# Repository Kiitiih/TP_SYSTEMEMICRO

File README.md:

CAMARA - DEMAN
3DN - TP1
---------------------------------------------------------------------------------------------------

rate baud 115200 db

13. PB9 est relié à la masse pour faire le boot_flash et donc il faut une resistance de pull-down

14. Il permet de faire le filtrage du 3.3v pour créer le 3.3VA

*******1.3. sCHÉMA
3. Page 3 / tableau operating conditions (0.47uF typ)

5. Page 15 (100n/10u)

6. CS : Chip Select (0 pour activer l'horloge)
   nLDAC : Latch Dac Input (sert à déclencher la transmission)

7. MISO n'est pas utilisé car il existe pas sur le DAC MCP4801

10. Page 19 datasheet STLINK V3 MINI

*******1.4. Affectation des empreintes

3. 0805, 0603, 1206 : c'est la taille des boitiers

4. LQFT (Low Pofile Quad Pad) : pin sur les 4 cotes du package avec un espacemenet variable mais une hauteur de 1.4mm

SOIC (Small Outline Integrated Circuit) : pin spacing 1.27mm qui sortent des deux cotés du composant

SOT-223 (Small Outline Transistor) : souvent utlisé pour les transistors et les diodes et souvent
3 pins

--------------------------------------------------------------------------------------------------------
3.1. Activation des LL drivers

2. Les différences observées c'est qu'on est plus proche du matériel donc il fut connaitre son microC donc l'intérêt c'est donne des accès direct au reagistre et donc il consomme moins en mémoire Flash et en mémoire dynamique

3.2 LED simple
2. Le prescaler vaut 255.
On a une freq de 32MHz sur les Timer et on veut une résolution sur 8 bits (on compte donc jusqu'à 255)
On fait 32MHz / 255 = 125,5MHz 
Donc prescaler = 125,5MHz / freq (1MHz)= 125
Avec counter period pour le PWM = 255

3.3 LED avec timer

La routine d'interruption se situe dans le fichier stm32L0xx_it.c. Ce qu'il manque par rapport au code genéré par la HAL, c'est la mise à 0 du flag d'interruption. C'est dramatique car si il ne repasse pas à 0, on ne sort jamais de l'interruption. Pour mettre le flag à 0, on utilise la fonction LL_TIM_ClearFlag_UPDATE(TIM21);

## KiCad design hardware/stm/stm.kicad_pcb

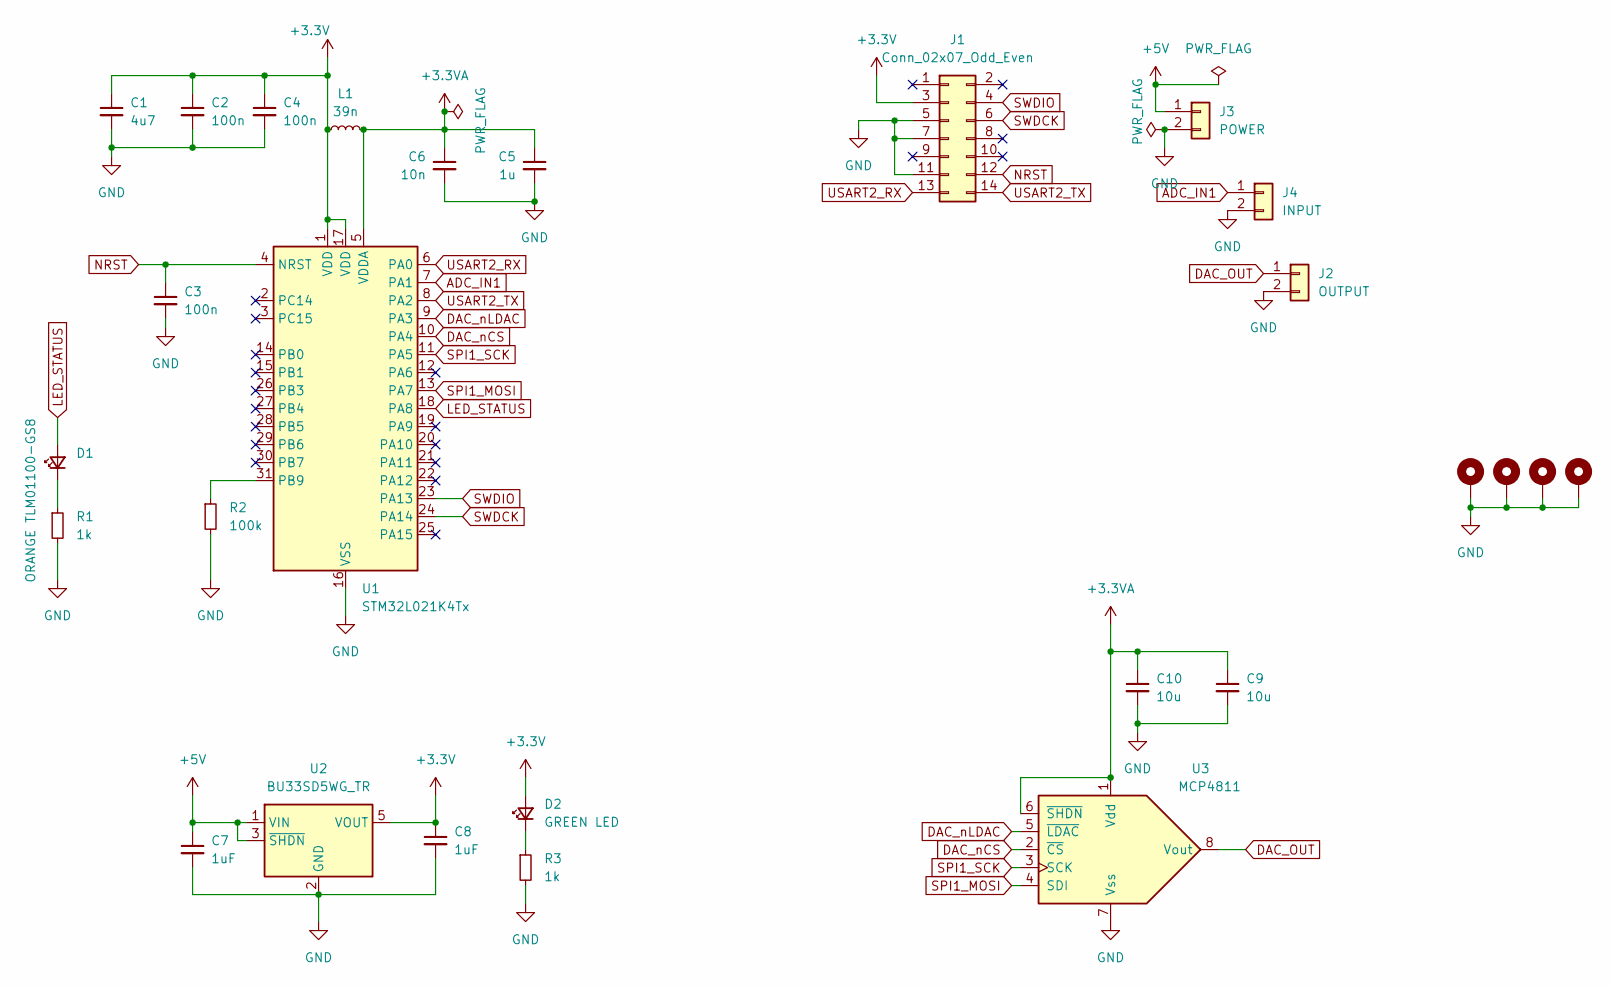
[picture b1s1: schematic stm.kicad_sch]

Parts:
C1: 4u7; LED_0603_1608Metric_Pad1.05x0.95mm_HandSolder
C2, C3, C4: 100n; C_0805_2012Metric_Pad1.18x1.45mm_HandSolder
C5: 1u; C_0805_2012Metric_Pad1.18x1.45mm_HandSolder
C6: 10n; C_0805_2012Metric
C7, C8: 1uF; C_0805_2012Metric
C9, C10: 10u; C_0805_2012Metric_Pad1.18x1.45mm_HandSolder
D1: ORANGE TLM01100-GS8; LED_0603_1608Metric_Pad1.05x0.95mm_HandSolder
D2: GREEN LED; LED_0603_1608Metric_Pad1.05x0.95mm_HandSolder
H101, H102, H103, H104: MountingHole_Pad; MountingHole_3.2mm_M3_Pad
J1: Conn_02x07_Odd_Even; PinHeader_2x07_P1.27mm_Vertical_SMD
J2: OUTPUT; JST_XH_B2B-XH-A_1x02_P2.50mm_Vertical
J3: POWER; JST_XH_B2B-XH-A_1x02_P2.50mm_Vertical
J4: INPUT; JST_XH_B2B-XH-A_1x02_P2.50mm_Vertical
L1: 39n; L_0805_2012Metric_Pad1.05x1.20mm_HandSolder
R1, R3: 1k; R_0805_2012Metric_Pad1.20x1.40mm_HandSolder
R2: 100k; R_0805_2012Metric_Pad1.20x1.40mm_HandSolder
U1: STM32L021K4Tx; LQFP-32_7x7mm_P0.8mm
U2: BU33SD5WG_TR; SOT-23-5
U3: MCP4811; SOIC-8_3.9x4.9mm_P1.27mm

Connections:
+3.3V: C1.1, C2.1, C4.1, C8.1, D2.2 (A), J1.3, L1.2, U1.1 (VDD), U1.17 (VDD), U2.5 (VOUT)
+3.3VA: C5.1, C6.1, C9.1, C10.1, L1.1, U1.5 (VDDA), U3.1 (Vdd), U3.6 (~SHDN)
+5V: C7.1, J3.1, U2.1 (VIN), U2.3 (~SHDN)
ADC_IN1: J4.1, U1.7 (PA1)
DAC_OUT: J2.1, U3.8 (Vout)
DAC_nCS: U1.10 (PA4), U3.2 (~CS)
DAC_nLDAC: U1.9 (PA3), U3.5 (~LDAC)
GND: C1.2, C2.2, C3.2, C4.2, C5.2, C6.2, C7.2, C8.2, C9.2, C10.2, H101.1, H102.1, H103.1, H104.1, J1.5, J1.7, J1.11, J2.2, J3.2, J4.2, R1.2, R2.2, R3.2, U1.16 (VSS), U1.32 (VSS), U2.2 (GND), U3.7 (Vss)
LED_STATUS: D1.2 (A), U1.18 (PA8)
NRST: C3.1, J1.12, U1.4 (NRST)
unnamed: D1.1 (K), R1.1
unnamed: D2.1 (K), R3.1
unnamed: R2.1, U1.31 (PB9)
SPI1_MOSI: U1.13 (PA7), U3.4 (SDI)
SPI1_SCK: U1.11 (PA5), U3.3 (SCK)
SWDCK: J1.6, U1.24 (PA14)
SWDIO: J1.4, U1.23 (PA13)
USART2_RX: J1.13, U1.6 (PA0)
USART2_TX: J1.14, U1.8 (PA2)

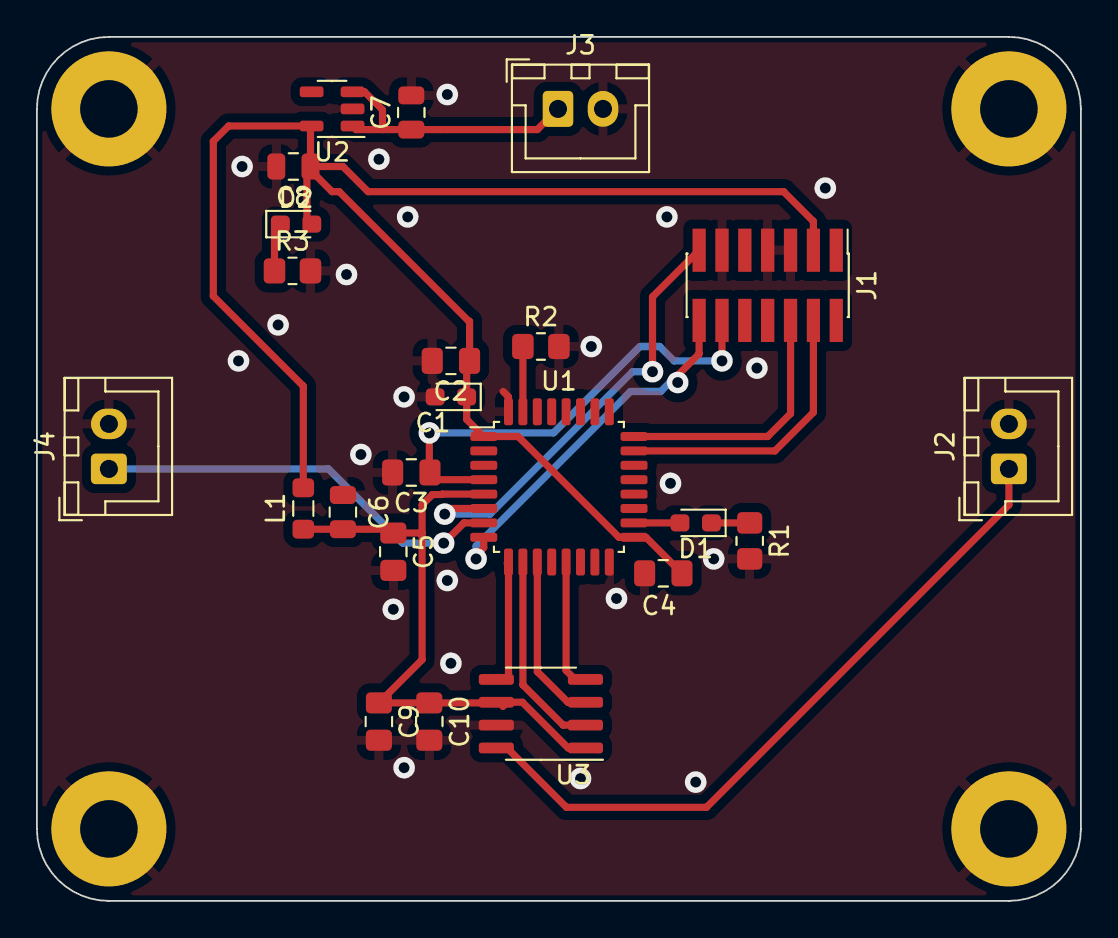
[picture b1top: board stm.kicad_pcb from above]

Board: 2 copper layers, 58.0 x 48.0 mm, 27 parts (0 on the bottom side), 19 nets.

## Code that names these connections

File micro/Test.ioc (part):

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Mcu.Name=STM32L021K4Tx
Mcu.Package=LQFP32
Mcu.UserName=STM32L021K4Tx
PA0-CK_IN.Mode=Asynchronous
PA0-CK_IN.Signal=USART2_RX
PA1.Mode=IN1
PA1.Signal=ADC_IN1
PA13.Mode=Serial_Wire
PA13.Signal=SYS_SWDIO
PA14.Mode=Serial_Wire
PA14.Signal=SYS_SWCLK
PA2.Mode=Asynchronous
PA2.Signal=USART2_TX
PA3.GPIOParameters=GPIO_Label
PA3.GPIO_Label=DAC_nLDAC
PA3.Signal=GPIO_Output
PA4.GPIOParameters=GPIO_Label
PA4.GPIO_Label=DAC_nCS
PA4.Signal=GPIO_Output
PA5.Mode=Full_Duplex_Master
PA5.Signal=SPI1_SCK
PA6.Mode=Full_Duplex_Master
PA6.Signal=SPI1_MISO
PA7.Mode=Full_Duplex_Master
PA7.Signal=SPI1_MOSI
PA8.Signal=S_TIM2_CH1
RCC.HSE_VALUE=8000000
RCC.SYSCLKFreq_VALUE=32000000
RCC.SYSCLKSource=RCC_SYSCLKSOURCE_PLLCLK
board=custom

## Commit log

2024-02-09 README
2024-02-29 pcb done
2024-03-14 Code
